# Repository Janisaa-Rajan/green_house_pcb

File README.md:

View this project on [CADLAB.io](https://cadlab.io/project/29237). 

# green_house_pcb

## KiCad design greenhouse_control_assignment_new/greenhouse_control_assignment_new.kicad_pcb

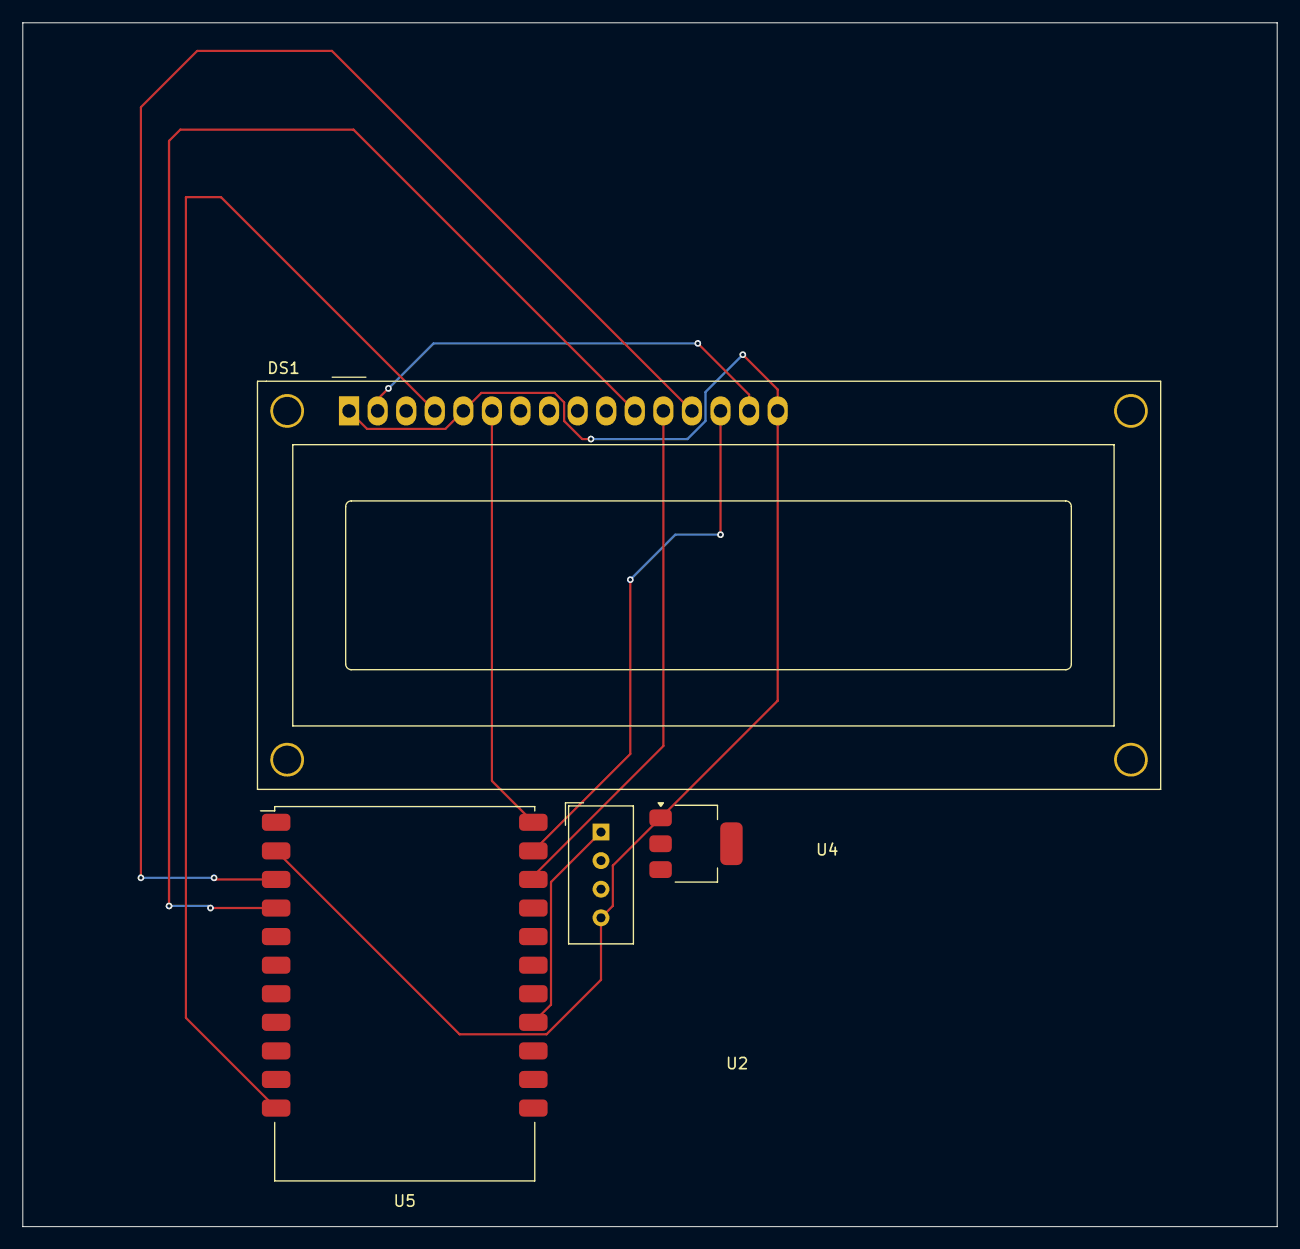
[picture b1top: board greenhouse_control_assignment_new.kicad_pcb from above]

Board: 2 copper layers, 111.5 x 107.0 mm, 4 parts (0 on the bottom side), 9 nets.

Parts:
DS1: WC1602A
U2: DHT11; Aosong_DHT11_5.5x12.0_P2.54mm
U4: AMS1117; SOT-223-3_TabPin2
U5: Olimex_MOD-WIFI-ESP8266-DEV

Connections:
+5V: DS1.2 (VDD), DS1.15 (LED(+))
/2: DS1.14 (D7), U5.21 (GPIO-0)
/3: DS1.13 (D6), U5.3 (GPIO1)
/4: DS1.12 (D5), U5.20 (GPIO-2)
/5: DS1.11 (D4), U5.4 (GPIO3)
/6: DS1.6 (E), U5.22 (GPIO4)
/7: DS1.4 (RS), U5.11 (GPIO5)
/18: U2.1 (VDD), U5.15 (GPIO16)
GND: DS1.1 (VSS), DS1.5 (R/W), DS1.16 (LED(-)), U2.4 (GND), U4.1 (ADJ), U5.2 (GND)

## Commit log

2025-04-10 Backlink to CADLAB.io has been added.
